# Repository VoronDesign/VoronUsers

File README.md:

# VoronUsers user mod repository

Welcome to VoronUsers. This is a place to share your mods for the VoronDesign 3D printers and find useful mods and resources from other Voron community members.

Check the [`printer_mods`](./printer_mods) folder for mods that apply to the current generation of printers. 

All mods that apply to older (=legacy) printers can be found in the [`legacy printers`](./legacy_printers) folder.

Mods where the authors have abandoned development can be found in the [`orphaned mods`](./orphaned_mods/) folder. If you want to start maintaining one of them, feel free to reach out via a [GitHub issue](https://github.com/VoronDesign/VoronUsers/issues/new/choose).

Looking to submit a mod? Check the [mod submission rules](https://github.com/VoronDesign/VoronUsers/wiki/Mod-Submission-Rules) and instructions on [how to submit to VoronUsers](https://github.com/VoronDesign/VoronUsers/wiki/How-to-Submit-to-VoronUsers)

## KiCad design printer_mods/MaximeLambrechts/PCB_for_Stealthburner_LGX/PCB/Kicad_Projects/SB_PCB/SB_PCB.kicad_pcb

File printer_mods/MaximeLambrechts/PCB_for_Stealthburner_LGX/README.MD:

# PCB for Voron Stealthburner & Bondtech LGX

This mod is a custom 2-piece PCB design, as well as a few printed parts, to make the Bondtech LGX fully compatible with the Voron Stealthburner.

This mod is based on two existing mods, all credits go to them for the initial design :

* LGX Stealthburner Mount Remix by Symataris on Thingiverse ([link here](https://www.thingiverse.com/thing:5242645))
* Stealthburner toolhead PCB by Hartk1213 ([link here](https://github.com/hartk1213/MISC/tree/main/PCBs/Stealthburner_Toolhead_PCB))

I really like the 2-piece PCB design by Hartk, with which you just plug the stealthburner in the main board via a connector, without having to deal with cables from the fans and LEDs.

Instead of trying to source different parts from different mods and make them all compatible with each other, I decided to create this mod and design 2 new PCB's (one for the stealthburner, one on the LGX), as well as the printed parts required to have a fully completed Stealthburner + LGX, as cleanly assembled as possible.

[1. Bill of Materials (BOM)](#1-bill-of-materials)

[2. Ordering PCBs](#2-ordering-pcbs)

[3. Printed parts](#3-printed-parts)

[4. Assembly Instructions](#4-assembly-instructions)

[5. Feedback](#5-feedback)

# 1. Bill of Materials (BOM)

Note: This BOM complements the original Stealthburner BOM. Only the extra compoments are included here. Items that are required for the original build are not included here. Refer to the stealthburner manual for a complete list of required components.

PCBs

* 1x Stealthburner side PCB (SB_PCB)
* 1x LGX side PCB (LGX_PCB)

Hardware

* 3x M3x6 Button head hex socket screws
* 1x 10mm standoff (female-female)
* 5x Heat set inserts (or 4 if using 2-hole cable chain)
* 1x M3x6 Socket head Cap Screws
* 2x M3x18 Socket head Cap Screws
* 2x M3x20 Socket head Cap Screws
* 2x M3x25 Socket head Cap Screws
* 2x M3x30 Socket head Cap Screws
* 2x M3x8 Flat head Screws (can be slightly longer, not critical)

Connectors & Electronics

* 1x Pin header, 6 pos, 2.54mm (Molex 22-28-4063)
* 1x Pin Socket, 6 pos, right angle through hole (Samtec SSW-106-02-G-S-RA)
* 1x Molex 43045-1600 (Board 16-pin receptacle)
* 1x Molex 43025-1600 (16-pin connector)
* 16x Molex 43030-0007 (contacts for wires)
* 2x Molex 43650-0200 (Hotend & Thermistor receptacles)
* 2x Molex 43645-0200 (Hotend & Thermistor connectors)
* 1x BAT85 diode (optional, if using probe only)
* 3x JST-PH 3-pin male & female
* 1x JST-PH 4-pin male & female

(Note: JST-PH connectors can be bought in assortment boxes on Amazon for example. I recommend this, as you would have multiple sizes in male/female in sufficient quantity for this and future projects, or should you need to recrimp a new cable for example)

Other

* 1x Small PTFE tube (2mm ID x 4mm OD) (length varies depending on your hotend. See assembly instructions).
* Small zipties

# 2. Ordering PCBs

Two Gerber zip files are provided for ordering the PCB's (**LGX_PCB_Gerber.zip** and **SB_PCB_Gerber.zip**).

I recommend JLCPCB or PCBWay for ordering the PCBs. I've personally ordered from JLCPCB and the boards were very cheap and worked perfectly.

An example order configuration for JLCPCB can be found [here](Pictures/PCB%20Order/JLCPCB.jpg).

An example order configuration for PCBWay can be found [here](Pictures/PCB%20Order/PCBWay.jpg).

Pay attention to the important settings (marked with an exclamation point) when ordering the PCB's!

The LGX PCB should be a **4-layer board of 1.6mm thickness**. (on JLCPCB only, you have to specify which layer is which, see picture)

The SB PCB should be a **2-layer board of 1.6mm thickness**.

Other parameters are personal preference, like the color of the board, or if you want lead-free HASL for example.

# 3. Printed parts

The following parts need to be (re)printed :

* **Stealthburner_Body.stl** (There are small differences to the original file. Some small cutouts for a better PCB fit and the PCB mounting
points have been modified.)
* **LGX_Mount.stl**
* **LGX_Rear_PCB_Support.stl**
* **Cover.stl**
* **Cable_Chain_Anchor_xHoles..stl** (Chose either the 2 or 3-hole version depending on your cable chain)

# 4. Assembly Instructions

Note: These instructions are a complement to the original Stealthburner assembly manual. Keep a copy of the original manual open in parallel 
to these instructions, as I will often refer to it.

## Preparing the PCBs

* Solder the components on the LGX pcb as shown on the picture. Make sure the 6-pin socket lays nice and flat on the PCB and is soldered straight. This is important for correct connection with the stealthburner later on.

* If you're not using an inductive probe (for example Klicky or KlickyNG mod with microswitch), replace the BAT85 diode by a small piece
of wire to short the pads. A leg from a donor component (LED or resistor for example) works well here.

* Install a 10mm standoff using an M3x6 button head screw.
Make sure the screw head **does not stick out more than 2mm from the PCB**.
Make sure **no solder points stick out more than 2mm**. (to avoid touching and potentially shorting on the LGX extruder motor later on)

* Solder a 6-pin header to the SB PCB. The pins should face up.

## Stealthburner

* Follow the original manual instructions to install the LED's and fans into the stealthburner body. Leave the cables hanging for now.

* Install the PCB into the SB body and fasten with 2 M3x6 button head screws.
**Warning**: Do not overtighten as these screw into plastic.

* Make sure the screws do not stick out of the SB body, or there would be a clearance issue with the LGX. (That's the reason why button head screws are used here instead of socket head)

* Solder all the wires onto the PCB as shown on the picture below. Note: The red (positive) wire of both fans can be soldered to either 24V or 5V 
depending on the voltage of your fans.

## Printhead

* Follow the stealthburner manual to assemble the printhead. You can print either the CW1 or CW2 version of the printed parts.

* Install the PTFE tube into the hotend. The length of the tube will vary depending on your hotend. The tube should stick out **25mm** from the top of the printed part.

## LGX

* Install 2 heat set inserts into the LGX Mount as shown. 
Install 2 (or 3) heat set inserts into the cable chain anchor as shown.

* dissasemble the front part of your LGX extruder.

* On the backside, remove the 2 left screws.

* Slide the LGX_Mount onto the LGX extruder and fasten with 2 M3x20 on the bottom and two M3x27 (original screws from LGX) on the front.

* Slide the PCB into the LGX_Mount printed parts grooves until it is fully seated into place.

* Install the PCB rear support printed part. It should slide onto the PCB and insert into the holes of the extruder motor.

* Install the cable chain anchor and fasten everything together with 2 M3x25 screws.

* Now is a good time to make sure no solder points touch the LGX extruder motor.

## Final Assembly

* Follow the stealthburner manual to install the carriage and probe (or klicky).

* Fasten the LGX assembly onto the carriage with 2 M3x30 screws.
Make sure the probe wires are routed correctly and are not pinched between the carriage and LGX.

* Slide the printhead from the bottom into the LGX assembly. Make sure it is fully inserted, flush with the LGX mount, and flush on the X-carriage.

* Slide the Stealthburner in place. Make sure the pins align correctly with the socket. It is recommended to first align and insert the pins, then slide the SB fully in place.

* Fasten the Stealthburner with 2 **M3x18** screws on top, and 2 **M3x50** screws on the bottom.

* Prepare a small cable for the extruder motor with JST-PH connectors as shown. Its length should be about **90mm**.

* Install the extruder motor cable.

* Wire up the rest of the components, including the hotend, thermistor, probe or switch, etc

* Fasten the cable chain with 2 M3x8 flat head screws.
Install a ziptie into the ziptie slot.

* Wire up and install the 16-pin connector. The wiring schematic is the same as the original Hartk PCB. The only difference is that the 14 and 2-pin connectors have been joined into a single 16-pin connector. The individual wires position is identical. See the wiring instructions [here](https://github.com/hartk1213/MISC/tree/main/PCBs/Stealthburner_Toolhead_PCB/Images/Wiring).

* Optionally, install a chamber thermistor. I've attached mine at the backside on the cable chain and routed the wires to the AUX connector on the PCB.

* Install the cover by sliding the backside over the M3 screws sticking out of the LGX, and then fasten on the side with 1 **M3x6** Socket head Screw.

## Done ! Happy printing!

# 5. Feedback

While I've manage to assemble everything on my printer, there may be issues I haven't thought of, mistakes on this page, or issues that will only arise after many hours of printing.

**USE THIS MOD AT YOUR OWN RISK!**

I'd appreciate any kind of feedback, good or bad.

If you encounter issues, please open an issue on this github page.

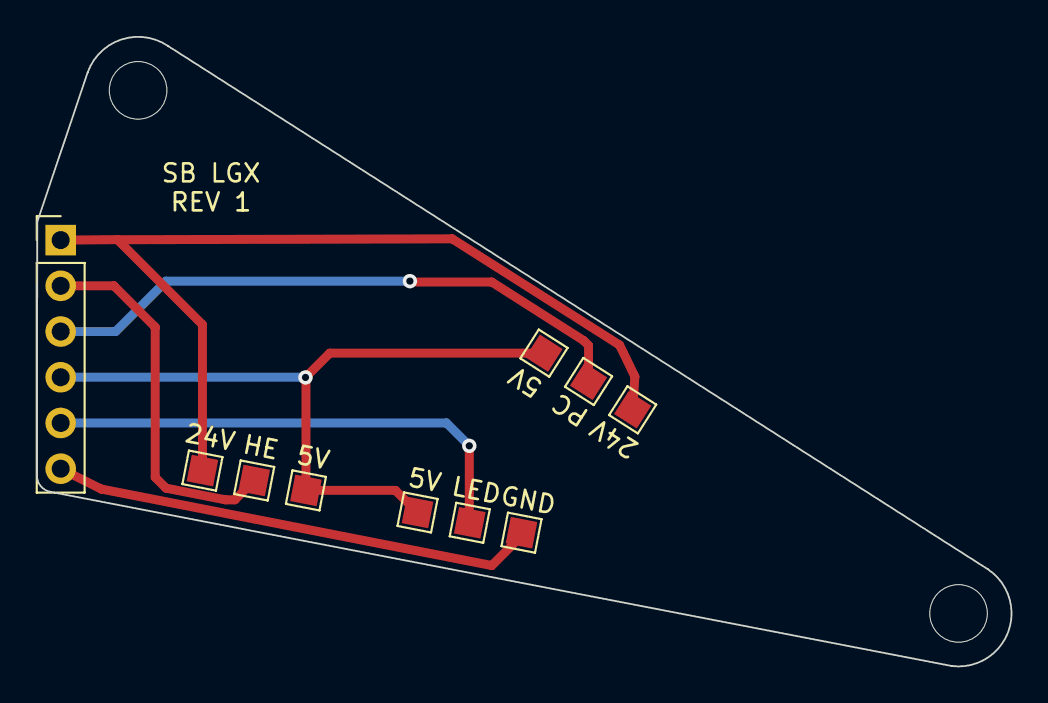
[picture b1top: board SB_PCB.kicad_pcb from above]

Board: 2 copper layers, 54.1 x 35.0 mm, 12 parts (0 on the bottom side), 6 nets.

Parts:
5V: 5V PC Fan; TestPoint_Pad_1.5x1.5mm
5V#2: 5V HE Fan; TestPoint_Pad_1.5x1.5mm
5V#3: Solder Pad 5V; TestPoint_Pad_1.5x1.5mm
24V: 24V HE Fan; TestPoint_Pad_1.5x1.5mm
24V#2: 24V PC Fan; TestPoint_Pad_1.5x1.5mm
GND: Solder Pad GND; TestPoint_Pad_1.5x1.5mm
H1, H2: MountingHole; MountingHole_3.2mm_M3
HE: GND HE Fan; TestPoint_Pad_1.5x1.5mm
J1: Pin Header; PinHeader_1x06_P2.54mm_Vertical
LED: Solder Pad LED; TestPoint_Pad_1.5x1.5mm
PC: GND PC Fan; TestPoint_Pad_1.5x1.5mm

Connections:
5V: 5V.1, 5V#2.1, 5V#3.1, J1.4
24V: 24V.1, 24V#2.1, J1.1
GND: GND.1, J1.6
HE FAN: HE.1, J1.2
LED: J1.5, LED.1
PC FAN: J1.3, PC.1

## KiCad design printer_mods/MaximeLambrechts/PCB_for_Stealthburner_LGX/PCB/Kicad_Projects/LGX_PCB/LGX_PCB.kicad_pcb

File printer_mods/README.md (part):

# Mods

Printer mods for Voron 3D printers
---

| Creator | Mod title | Description | Printer compatibility | Last Changed |
| --- | --- | --- | --- | --- |
| 1-0-R | [V2.4 handle](1-0-R/handle) | Handle for Voron 2.4 | V2.4 | 2024-01-08T16:38:25+00:00 |
| 120decibell | [Side entry exhaust housing](120decibell/exhaust_housing_side_entry) | Exhaust housing with dual cover screws and single or dual side... | V1.8, V2.4, VT | 2024-01-08T16:38:25+00:00 |
|  | [Huvud Chain Mount](120decibell/huvud_chain_mount) | Huvud rear mount for Clockwork or LGX that supports a cable chain. | V1.8, VT | 2024-01-08T16:38:25+00:00 |
| 3dpandme | [FANnypack zero](3dpandme/Fannypack_zero) | Electronics cooling solution for Voron Zero | V0.2, VSW, VT | 2024-01-08T16:38:25+00:00 |
|  | [Thermistor holder zero](3dpandme/Thermistor_holder_zero) | Extended thermistor holder for Voron Zero | V0.2, VSW, VT | 2024-01-08T16:38:25+00:00 |
| 3vilson | [V0.1_Skirt_Holes](3vilson/V0.1_Skirt_Holes) | Skirt with Access Holes from the bottom | V0.2 | 2024-01-08T16:38:25+00:00 |
|  | [V0.1_Skirt_Inlet](3vilson/V0.1_Skirt_Inlet) | Skirt with C14 inlet + New feet to screw into | V0.2 | 2024-01-08T16:38:25+00:00 |
| 42bios | [Corner panel clip w. cable](42bios/corner_panel_clip_cable) | Corner panel clip with an internal cable path. | V2.4 | 2024-01-08T16:38:25+00:00 |
|  | [Exhaust filter housing - side...](42bios/exhaust_filter_housing_side) | Exhaust filter housing with the G1-8 "thread on the side. | V2.4 | 2024-01-08T16:38:25+00:00 |
|  | [relay mount](42bios/relay_mount) | relay-mount for 2x 2 channel relay modules. | V2.4 | 2024-01-08T16:38:25+00:00 |
| ademuri | [Lights, Camera, Voron](ademuri/Lights_Camera_Voron) | A mount for LED strips and Picam for the V0.1 | V0.2 | 2024-01-08T16:38:25+00:00 |
| aeresov | [Ballpoint pen spring DIN clips](aeresov/ballpoint-pen-spring-DIN-clips) | Assortment of mechanical DIN clips using common ballpoint pen springs. | V2.4r2, VT | 2024-06-19T10:47:27+00:00 |
|  | [cable tie DIN mount](aeresov/cable_tie_DIN_mount) | A bracket for cable ties to route cables across DIN rails. | V2.4 | 2024-01-08T16:38:25+00:00 |
|  | [MeanWell UHP-xxx DIN mount](aeresov/MeanWell_UHP_DIN_mount) | A bracket for MeanWell UHP series PSU (200, 350 and 500) to mount... | V2.4 | 2024-01-08T16:38:25+00:00 |
|  | [Raspberry Pi DIN mount](aeresov/Raspberry_Pi_DIN_mount) | A bracket for Raspberry Pi 3/4 to mount it onto DIN rail, along or... | V2.4 | 2024-01-08T16:38:25+00:00 |
|  | [SKR 1.3/1.4 DIN mount](aeresov/SKR_DIN_mount) | A bracket for SKR 1.3/1.4 board to mount it onto DIN rail, along or... | V2.4 | 2024-01-08T16:38:25+00:00 |
|  | [TL filament sensor bracket](aeresov/TL_filament_sensor_bracket) | A bracket for TL filament sensor to mount near stock spool holder. | V2.4 | 2024-01-08T16:38:25+00:00 |
| Akio | [Hidden cable routing z belt cover](Akio/cable_routing_z_belt_cover) | Z belt covers that allow hidden cable routing. | V2.4 | 2024-01-08T16:38:25+00:00 |
| al3ph | [Analog Timer Mount](al3ph/analog_timer_mount) | A skirt mount for analog timer | V0.2 | 2024-01-08T16:38:25+00:00 |
|  | [Filament Runout Sensor](al3ph/filament_runout) | A simple filament runout sensor | V0.2, V1.8, V2.4, VSW | 2024-01-08T16:38:25+00:00 |
|  | [LED Mount](al3ph/led_mount) | A mount for 10mm LED WS2812 strips | V0.2 | 2024-01-08T16:38:25+00:00 |
|  | [PL05 Sensor Mount](al3ph/pl05_mount) | A mount PL05 inductive sensor | V0.2 | 2024-01-08T16:38:25+00:00 |
| alanho | [BTT PITFT50 v2 Mount](alanho/BTT_PITFT50_v2_Mount) | A mount for the BTT PITFT50 v2 Touch Display | V2.4 | 2024-01-08T16:38:25+00:00 |
| albert | [IKEA Dioder Led Mount](albert/IKEA_Dioder_Led_Mount) | A mount for the IKEA Dioder LED strip | V2.4 | 2024-01-08T16:38:25+00:00 |
| AlexanderT-Moss | [270 Clamping Hinges](AlexanderT-Moss/270-Clamping-Hinges) | Simple 270 degree hinges that clamp to the front panels instead of... | V2.4 | 2024-01-08T16:38:25+00:00 |
| Andre | [Mini Afterburner ADXL345 Mount](Andre/Mini_Afterburner_ADXL345_Mount) | Mount for an AXDL345 on the Mini Afterburner | V0.2 | 2024-01-08T16:38:25+00:00 |
|  | [Mini Afterburner Strain Relief](Andre/Mini_Afterburner_Strain_Relief) | A replacement strain relief for the Mini Afterburner toolhead | V0.2 | 2024-01-08T16:38:25+00:00 |
|  | [Revo Nozzle Skirt](Andre/Revo_Nozzle_Skirt_Trident) | A Revo nozzle box hidden in a Trident skirt. | VT | 2024-01-08T16:38:25+00:00 |
|  | [V0 Neopixel Front Bed Mount](Andre/V0_Neopixel_Front_Bed_Mount) | A replacement Front Bed Mount with room for a neopixel or dotstar... | V0.2 | 2024-01-08T16:38:25+00:00 |
| antoinecellerier | [DS18B20 Sensor Mount](antoinecellerier/ds18b20-sensor-mount) | DS18B20 temperature sensor mount | V0.2 | 2024-01-08T16:38:25+00:00 |
| ardichoke | [V0 Long Thumb Nut](ardichoke/v0-long-thumb-nut) | Taller thumb nuts for V0 bed | V0.2 | 2024-01-08T16:38:25+00:00 |
| arkeet | [Dial test indicator mount](arkeet/dti-mount) | A toolhead mount for a dial test indicator, where the tip is... | V1.8, V2.4 | 2024-01-08T16:38:25+00:00 |
|  | [Magnetic hotend fan cover](arkeet/magnet-fan-cover) | A replacement hotend fan cover, held with magnets instead of screws. | V1.8, V2.4, VSW | 2024-01-08T16:38:25+00:00 |
|  | [MGN12 X-axis](arkeet/mgn12) | Replaces the dual MGN9H rails with a single MGN12H. | V2.4 | 2024-01-08T16:38:25+00:00 |
|  | [V0 DC inlet](arkeet/v0-dc-inlet) | Skirt inlet for external 24V DC power supply. | V0.2 | 2024-01-08T16:38:25+00:00 |
| aTinyShellScript | [RS PSU DIN Bracket](aTinyShellScript/RS_PSU_DIN_Brackets) | DIN brackets for MeanWell RS PSUs with 80mm spacing. | V2.4 | 2024-01-08T16:38:25+00:00 |
| AVieira | [Universal_Phone_Mount](AVieira/Universal_Phone_Mount) | This mod allows the use of different smartphones or possibly... | V2.4r2 | 2024-01-08T16:38:25+00:00 |
| baccula | [Revo Nozzle Holder for v2.4 350](baccula/revo_skirt_nozzle_holder) | A remix of Andre's design allowing for skirt storage of 4 E3D Revo... | V2.4 | 2024-01-08T16:38:25+00:00 |
| Backenfutter | [Mount for Electreeks Camera](Backenfutter/Mount_for_Electreeks_Camera) | This Mod is a simple "One Piece" mount for the popular Electreeks... | V2.4 | 2024-01-08T16:38:25+00:00 |
| Badnoob | [AB-BN Afterburner mod (5015)](Badnoob/AB-BN) | Improved Afterburner with 5015 fan | V1.8, V2.4, VSW, VT | 2024-01-08T16:38:25+00:00 |
|  | [AB-BN for Stock Afterburner (4020)](Badnoob/ABBN_for_Stock) | Improved Dragon and Rapido toolhead for stock Afterburner with 4020... | V1.8, V2.4, VSW, VT | 2024-01-08T16:38:25+00:00 |
|  | [Precision AB Drive](Badnoob/Precision_AB_Drive) | Changes the gearing for the AB drives to improve both resolution... | V2.4 | 2024-01-08T16:38:25+00:00 |
| Baltojikale | [LoudOwl aka Stabby](Baltojikale/LoudOwl_aka_Stabby) | Alternative dual 5015 part cooling fan toolhead for Afterburner | V1.8, V2.4, VSW | 2024-01-08T16:38:25+00:00 |
| beaugalbraith | [Nova Printhead](beaugalbraith/Nova_Printhead) | Use Nova Hotend with Afterburner | V2.4 | 2024-01-08T16:38:25+00:00 |
| BladeScraper-Designs | [CornerPanel_SpoolHolder](BladeScraper-Designs/CornerPanel_SpoolHolder) | A better supported Spool Holder that mounts to a modified corner... | V0.2 | 2024-01-08T16:38:25+00:00 |
|  | [Horizontal Spool Holder](BladeScraper-Designs/Horizontal-Spool-Holder) | Based on the stock holder but mounts to the horizontal extrusions. | V2.4 | 2024-01-08T16:38:25+00:00 |
|  | [Microswitch Pod With Connector](BladeScraper-Designs/Microswitch_Pod_With_Conector) | Microswitch pod with JST-XH 4-pin connector | V2.4 | 2024-01-08T16:38:25+00:00 |
| Blamm | [LRS-100 DIN mount](Blamm/lrs-100) | DIN rail mount for an extra LRS-100 Power Supply | V1.8, V2.4, VT | 2024-01-08T16:38:25+00:00 |
| BlueBear | [Bowden Fence](BlueBear/Bowden_Fence) | A little "fence" to hold the tubes away from the belts. | V0.2 | 2024-01-08T16:38:25+00:00 |
|  | [Deck Panel Backpack](BlueBear/Deck_Panel_Backpack) | A mounting alternative if you don't want to drill your deck panel | V0.2 | 2024-01-08T16:38:25+00:00 |
|  | [Clippable Wago 221 Mounts](BlueBear/Wago_221_mount) | Mounts for Wago 221 to screw or clip-in on 1515 extrusions | V0.2 | 2024-01-08T16:38:25+00:00 |
|  | [Ziptie Mount](BlueBear/Ziptie_Mount) | Clippable Ziptie hooks for 1515 extrusions | V0.2 | 2024-01-08T16:38:25+00:00 |
| bobbleheed | [Filament Runout Sensor](bobbleheed/Filament_Runout) | Filament runout sensor that replaces the stock bowden retainer | V1.8, V2.4, VT | 2024-01-08T16:38:25+00:00 |
|  | [Magnetic Panels](bobbleheed/Magnetic_Panels) | Magnetic clips to allow for easy removal and installation of panels | V2.4 | 2024-01-08T16:38:25+00:00 |
| Boingomw | [Wago mount](Boingomw/Wago_mount) | Smaller 5 port Wago mount that fits parallel to the support rails | V2.4 | 2024-01-08T16:38:25+00:00 |
| Bondtech | [Mini-After-LGX-Lite](Bondtech/Mini-After-LGX-Lite) | LGX Lite Toolhead Setup For Voron V0.1. | V0.2 | 2024-01-08T16:38:25+00:00 |
| btp | [Galileo chain mount (befenybay)](btp/Galileo_Switchwire_Chain_Mount) | Modified chain mount position to cater for difference with Galileo... | VSW | 2024-01-08T16:38:25+00:00 |
| buzzdalf | [v1.8/2.4 Afterburner connector...](buzzdalf/connector_cover) | v1.8/2.4 Connector cover for 42STH20-1004AS | V1.8, V2.4 | 2024-01-08T16:38:25+00:00 |
|  | [Ender 3 Switchwire Taller Z Mod](buzzdalf/ender_switchwire_taller_z) | Taller Z Mod | VSW | 2024-01-08T16:38:25+00:00 |
|  | [Ender 3 Switchwire Y Tensioner Mod](buzzdalf/ytension) | Y Tension Mod | VSW | 2024-01-08T16:38:25+00:00 |
| ByteChild | [2-Channel Relay DIN Rail Bracket](ByteChild/2_Channel_Relay_DIN_Rail_Bracket) | DIN Rail mounting bracket for an 2-Channel-Relay | V2.4 | 2024-01-08T16:38:25+00:00 |
|  | [ESP32 DIN Rail Bracket](ByteChild/ESP32_DIN_Rail_Bracket) | DIN rail mounting bracket for an ESP32 | V2.4 | 2024-01-08T16:38:25+00:00 |
| bythorsthunder | [MGN9 Backers Idlers](bythorsthunder/MGN9_Backers) | New idler uppers for MGN9 Extrusion backers | V2.4 | 2024-01-08T16:38:25+00:00 |
|  | [Stealthburner Rapido UHF](bythorsthunder/Stealthburner_Rapido_Uhf) | Stealthburner mod for Rapido UHF | V2.4, VSW, VT | 2024-01-08T16:38:25+00:00 |
| CannedBass | [PITFT50 45-degree mount](CannedBass/PITFT50_45_degree_mount) | Mount that puts the screen at a 45-degree angle for more vertical... | V2.4, VT | 2024-01-08T16:38:25+00:00 |
|  | [Trident Bed Fans](CannedBass/Trident_Bed_Fans) | Bed fans for Trident | VT | 2024-01-08T16:38:25+00:00 |
| Ch4rlesB | [V0 Handles Slim](Ch4rlesB/V0_Handles_Slim) | Simple and slim handles for the V0 | V0.2 | 2024-01-08T16:38:25+00:00 |
| ChenTheDesignMaker | [Z Belt Clip](ChenTheDesignMaker/Z_Belt_Clip) | Simple clip to keep extra Z belts clean and away from panels | V2.4 | 2024-01-08T16:38:25+00:00 |
| chirpy | [V0.1 Nozzle Wiper](chirpy/NozzleWiper) | Servo powered nozzle wiper and purge bucket | V0.2 | 2024-01-08T16:38:25+00:00 |
|  | [Runout UnKlicky Sensor](chirpy/RunoutUnklicky) | Runout UnKlicky Sensor is a filament runout sensor with mounts for... | V0.2, V1.8, V2.4, VSW, VT | 2024-01-08T16:38:25+00:00 |
|  | [V0.1 Raised Tophat](chirpy/TipTophat) | Alternative Tophat design that uses stock panels and raises height... | V0.2 | 2024-01-08T16:38:25+00:00 |
| chri.kai.in | [20x20mm Profile Covers](chri.kai.in/20x20mm_Profile_Covers) | Provide overlapping and flush slot covers for 20x20mm slot6... | V1.8, V2.4, VSW, VT | 2024-01-08T16:38:25+00:00 |
|  | [Angry CAM USB](chri.kai.in/Angry_CAM_USB) | Housing for small USB camera module, allowing mounting to gantry or... | V2.4 | 2024-01-08T16:38:25+00:00 |
|  | [Exhaust Adapter 100mm](chri.kai.in/Exhaust_Adapter_100mm) | Replace 60mm exhaust fan with 100mm ventilation system adapter | V1.8, V2.4, VT | 2024-01-08T16:38:25+00:00 |
| chrisrgonzales | [270° Front Panel Hinge](chrisrgonzales/270_degree_hinge) | Hinges that have 270° of swivel, parametric CAD included | V2.4 | 2024-01-08T16:38:25+00:00 |
| christophmueller | [Phaetus and Zodiac Dragonfly BMO...](christophmueller/Phaetus_Dragonfly_BMO_Afterburner) | Covers both the original Phaetus variant as well as the Zodiac one. | V1.8, V2.4, VSW | 2024-01-08T16:38:25+00:00 |
| claytono | [Voron 2.4 Extrusion Jig](claytono/2.4-extrusion-jig) | A jig help align extrusions to get a properly square frame | V2.4 | 2024-01-08T16:38:25+00:00 |
|  | [Fysetc S6 V2 Mount](claytono/fysetc-s6-v2-mount) | DIN Mount for the Fysetc S6 V2 controller | V1.8, V2.4 | 2024-01-08T16:38:25+00:00 |
|  | [V0 Zip Tie Skirts](claytono/v0-zip-tie-skirts) | V0 skirts with small loops added along the top to allow zip tyiing... | V0.2 | 2024-01-08T16:38:25+00:00 |
| clee | [Monster8 DIN Rail Mounts](clee/Monster8_heatsert_mount) | DIN mount for Makerbase Monster8 V1/V2 controller | V2.4, VT | 2024-01-08T16:38:25+00:00 |
| cmrny | [V0.1 Motor Panel Modification](cmrny/v01_motor_panel_no_rub) | V0.1 Motor panel modification to keep umbilical and bowden tube... | V0.2 | 2024-01-08T16:38:25+00:00 |
| conqueror433 | [Voron Parts Logo](conqueror433/Voron_Parts_Logo) | Voron Parts Logo for your back panels, 3D Print or Laser Cut | V2.4 | 2024-01-08T16:38:25+00:00 |
|  | [Voron V0.1 Parts Logo](conqueror433/Voron_V0.1_Parts_Logo) | Voron Parts Logo for your V0 deck panel | V0.2 | 2024-01-08T16:38:25+00:00 |
| consibonsi | [Y-Mod SW 9mm](consibonsi/Y-Mod_SW_9mm) | 9mm Y belt mod for SW | VSW | 2024-01-08T16:38:25+00:00 |
| crackzero_akl | [RapidoTZ Hotend Stealthburner](crackzero_akl/RapidoTZ_Hotend) | Construction Guide to transform Bambu Lab TZ 2.0 hotend to Rapido V2.0-like hotend | V0.2, V1.8, V2.4, VT, VSW | 2024-01-08T16:38:25+00:00 |
| csch0 | [SW Fan Mount No Tape](csch0/SW_FanMount_No_Tape) | 60x20 Fan Mount for SW without tape | VSW | 2024-01-08T16:38:25+00:00 |
| d3nny | [Filtered Power Plug with...](d3nny/mains_plug_panel_for_RND_165-00057) | Filtered Power Plug for RND 165-00057 and CAT6-Plug | V2.4 | 2024-01-08T16:38:25+00:00 |
| D4rkCelerity | [Raspberry Pi Zero Bracket](D4rkCelerity/Raspberry_Pi_Zero_Bracket) | Modified version of Trident RPi bracket to fit the smaller RPi Zero | V0.2, V1.8, V2.4, VT | 2024-01-08T16:38:25+00:00 |
| DaGlo | [V0.1 Duet 2 Wifi mounting brackets](DaGlo/Voron_V0_Duet_2_WiFi_Mounting_Brackets) | Voron 0.1 Mounting brackets with/without RPi 4 | V0.2 | 2024-01-08T16:38:25+00:00 |
|  | [Voron V0 Mean Well power supply...](DaGlo/Voron_V0_MW_PS_Bracket) | Voron V0 Mean Well power supply bracket (Funssor Kit) | V0.2 | 2024-01-08T16:38:25+00:00 |
|  | [Voron V0 SSR Mount](DaGlo/Voron_V0_SSR_Mount) | Voron V0 SSR Mount for the bottom | V0.2 | 2024-01-08T16:38:25+00:00 |
| DaGrooch13 | [Tophat Exhaust Filter V0](DaGrooch13/Tophat_Exhaust_Filter) | Activated charcoal exhaust filter with HEPA that replaces the rear... | V0.2 | 2024-01-08T16:38:25+00:00 |
| Dan88 | [V0 one-part Skirts](Dan88/V0skirt) | One part Skirts for the V0 | V0.2 | 2024-01-08T16:38:25+00:00 |
| dankeeling | [Creative Live! Camera Mount](dankeeling/CreativeLiveCameraMount) | A mod to provide a mount for the Creative Live! Camera that mounts... | V2.4r2, VT | 2024-01-08T16:38:25+00:00 |
| DaStivi | [The Cephalopod limb (BTT Octopus...](DaStivi/the_Cephalopods_limb) | An alternative Din rail mount for BTT Octopus (PRO) boards | V1.8, V2.4, VSW, VT | 2024-01-08T16:38:25+00:00 |
| Daten | [Revo hotend skirt case](Daten/Voron_2.4_Revo_Nozzle_Holder) | A skirt case for the Revo hotends to reside R1 and R2 | V2.4 | 2024-01-08T16:38:25+00:00 |
| davidauvergne | [Center_cable_management_duct](davidauvergne/Center_cable_management_duct) | Mod for a centered cable management | V2.4 | 2024-01-08T16:38:25+00:00 |
| DC67 | [Plug Panel Mod for Schaffner...](DC67/plug_panel_schaffner) | A modified plug panel for the Power Entry Connector Schaffner... | V2.4 | 2024-01-08T16:38:25+00:00 |
| deepfriedheroin | [v0 Wago Bed Mounts](deepfriedheroin/v0_bed_wagos) | Easy to install Wago mounts for the v0 | V0.2 | 2024-01-08T16:38:25+00:00 |
|  | [v0 Power Wagos](deepfriedheroin/v0_power_wagos) | Easy to install Wago mounts for v0 mains | V0.2 | 2024-01-08T16:38:25+00:00 |
|  | [V2 Bed Wagos](deepfriedheroin/v2_bed_wagos) | Wire management for the v2 bed | V2.4 | 2024-01-08T16:38:25+00:00 |
| dePrintinator | [HEPA Exhaust](dePrintinator/HEPA_Filter_Exhaust) | HEPA filter chamber exhaust replacement. | V1.8, V2.4, VT | 2024-01-08T16:38:25+00:00 |
| DerekBackus | [LED Strip Holder](DerekBackus/LED_Holder) | Simple bracket to mount an LED strip | V2.4, VT | 2024-01-21T20:17:15+00:00 |
|  | [Trident Right Skirt Switch](DerekBackus/Right_Skirt_Switch) | Moves power switch to right front skirt on the Trident | VT | 2024-01-21T20:17:15+00:00 |
| Derpimus | [V0.1 Block Handle](Derpimus/Block_handle_v0.1) | V0.1 Block Style Handle | V0.2 | 2024-01-08T16:38:25+00:00 |
| DorjeDorf | [Duet 3 3HC Din Bracket](DorjeDorf/Duet_3_3HC_Din_Bracket) | V2.4 Duet 3 3HC Din Bracket | V2.4 | 2024-01-08T16:38:25+00:00 |
|  | [Duet 3 6HC Din Bracket](DorjeDorf/Duet_3_6HC_Din_Bracket) | V2.4 Duet 3 6HC Din Bracket | V2.4 | 2024-01-08T16:38:25+00:00 |
| doubletrouble | [V0 Skirt Mod](doubletrouble/V0_Skirt_Mod) | V0 Skirt Mod | V0.2 | 2024-01-08T16:38:25+00:00 |
| Dr-Info | [BTT 5160T Plus Mounts](Dr-Info/BTT_5160T_Plus_Mounts) | Mounts for BTT 5160T Plus to DIN, 2020 and 1515 | V2.4, VT | 2024-02-01T10:07:10+00:00 |
|  | [Corner Cable Cover with Drop Holes](Dr-Info/corner_cable_cover_with_drop_down_holes) | Corner cable cover around Z-idler with drop holes near z frame and... | V2.4, VT | 2024-02-01T10:07:10+00:00 |
|  | [Lever Connector Mount Side Fan...](Dr-Info/Lever_Connector_Mount_Side_Fan_Support) | Mount Universal Lever Connectors or WAGO 221 using the side fan... | V2.4, VT | 2024-02-01T10:07:10+00:00 |
|  | [LRS DIN Mount Offset](Dr-Info/LRS_DIN_Mount_Offset) | Offset mount for LRS PSU on DIN rail with stabilizer | V2.4, VT | 2024-02-01T10:07:10+00:00 |
|  | [V2.4 Z Drive Motor Tensioner Mod](Dr-Info/V2.4_z_drive_motor_tensioner_mod) | Braced motor tensioner for z drive | V2.4r2 | 2024-02-23T17:05:57+00:00 |
|  | [V2.4 Rear Skirt Mod for Z-Drive...](Dr-Info/V2.4r2_Z-Drive_Motor_Tensioner_Mod_Rear_Skirts) | This mod enables the you to utilize the rear skirts, power and... | V2.4 | 2024-01-08T16:38:25+00:00 |
| DrGhetto | [Ghetto Panels](DrGhetto/GhettoPanels) | Printed panels for the Voron Zero | V0.2 | 2024-01-08T16:38:25+00:00 |
| eamars | [Stealthburner (RC1) Dragon...](eamars/stealthburner_crazy_dragon_toolhead) | The Stealthburner toolhead mount for Mellow Crazy, TriangleLab... | V1.8, V2.4, VSW, VT | 2024-01-08T16:38:25+00:00 |
| eddie | [LED Bar Clip](eddie/LED_Bar_Clip) | Modular LED Clip for mounting LED Strip to 2020 Extrusions | V1.8, V2.4, VT | 2024-01-08T16:38:25+00:00 |
|  | [V1.8 12mm Z Mod](eddie/V1.8_12mm_Z_Mod) | Add V1.8 option for 12mm Z rods | V1.8 | 2024-01-08T16:38:25+00:00 |
| edwardyeeks | [Tridentified V2.4 Power Inlet](edwardyeeks/Tridentified_V2.4_Power_Inlet) | Trident style side power inlet for V2.4 using Z Drive Motor... | V2.4 | 2024-01-08T16:38:25+00:00 |
| elcrni | [Trident Internal Spool Holder](elcrni/Trident_Internal_Spool_Holder) | Internal spool holder for 300 and 350 Tridents. Supports full size... | VT | 2024-01-08T16:38:25+00:00 |
|  | [V.24/Trident Spool Holder](elcrni/V2.4-Trident-Spool-Holders) | Spool holder that mounts on top for "too close to the wall" printers | V1.8, V2.4, VT | 2024-01-08T16:38:25+00:00 |
| Electroleon | [U2C Mounting](Electroleon/U2C_Mounting) | Bigtreetech U2C CAN Interface mounting bracket | V0.2, V1.8, V2.4, VT | 2024-01-08T16:38:25+00:00 |
| Ellis | [15x15 Drag Chain End](Ellis/15x15_Drag_Chain_End) | 15x15 drag chain end piece | V2.4 | 2024-01-08T16:38:25+00:00 |
|  | [Badge Retractor Mount](Ellis/Badge_Retractor_Mount) | Extrusion mount for badge retractor to keep bowden tube out of the... | V2.4 | 2024-01-08T16:38:25+00:00 |
|  | [Bed Fans](Ellis/Bed_Fans) | Bed fan control macros and 5015 bed fan mounts | V2.4 | 2024-01-08T16:38:25+00:00 |
|  | [Short Z Joints](Ellis/Short_Z_Joints) | Shorter Z joints for the v2.4 | V2.4 | 2024-01-08T16:38:25+00:00 |
|  | [Single MGN9H Carriage](Ellis/Single_MGN9H_Carriage) | Single MGN9H toolhead carriage with toolhead x endstop support (for... | V1.8, V2.4 | 2024-01-08T16:38:25+00:00 |
| ElPoPo | [Removable Doors](ElPoPo/RemovableDoors) | New hinge to easily remove the door and have a wide opening V2.x | V2.4 | 2024-01-08T16:38:25+00:00 |
| EmJay276 | [Stealthburner Phaetus Dragon UHF...](EmJay276/stealthburner_dragon_UHF_toolhead) | This mod adds a tool cartridge for the Phaetus Dragon UHF and... | V2.4, VT | 2024-01-08T16:38:25+00:00 |
| Empusas | [Mounts for BTT Filament Motion...](Empusas/BTT_Filament_Motion_Sensor_Mount) | Mounts for Big Tree Tech Smart Filament Motion Sensor | V0.2, V1.8, V2.4, VSW | 2024-01-08T16:38:25+00:00 |
|  | [Power Skirt 2.x FN284-10-06](Empusas/PowerSkirt_FN284-10-06) | Power Skirt for Schaffner FN284-10-06 V2.x | V2.4 | 2024-01-08T16:38:25+00:00 |
|  | [Mounts for Terminal Blocks NC933...](Empusas/Terminal_Blocks_NC933_SPL-62) | Mounts for Terminal Blocks NC933 and SPL-62 from AliExpress | V2.4 | 2024-01-08T16:38:25+00:00 |
| evandepol | [Crydom GN Terminal Guard](evandepol/Crydom-GN-Guard) | A simple safety guard for the terminals on a Crydom GN SSR | V2.4 | 2024-01-08T16:38:25+00:00 |
|  | [Voron 2.4 cable clamps](evandepol/Voron2.4-Cable-clamps) | A set of 2020-mounted cable guards to organize and dress the wiring... | V2.4 | 2024-01-08T16:38:25+00:00 |
| falo | [LGX Lite CAN Side Mount](falo/lgx_lite_side_can) | A side mounting for a CAN board (Huvud/SHT42) to the LGX Lite | V1.8, V2.4, VSW, VT | 2024-01-08T16:38:25+00:00 |
|  | [Magnetic Exhaust Grill Cover](falo/magnetic_grill_cover) | A magnetic cover to seal the filtered exhaust | V2.4 | 2024-01-08T16:38:25+00:00 |
|  | [Toolhead PCB to CAN Mount Adaptor](falo/toolhead_pcb_to_can) | A mount to enable side mounting of a CAN board (Huvud/SHT42) in... | V1.8, V2.4, VSW, VT | 2024-01-08T16:38:25+00:00 |
| Ferdi360 | [2.4 Bedfan Backplates](Ferdi360/2.4_Bedfan_Backplates) | Backplates for your Voron 2.4 that block hot air out of your... | V2.4r2 | 2024-01-08T16:38:25+00:00 |
| Fiction | [C270 mount](Fiction/C270_mount) | Logitech C270 webcam front-centre mount | V2.4, VT | 2024-01-08T16:38:25+00:00 |
|  | [Crossrail](Fiction/Crossrail) | Across-the-rails LRS-200-24 or RSP-200-24 mount using DRP-03 brackets | V2.4, VT | 2024-01-08T16:38:25+00:00 |
|  | [Exhaust_cover](Fiction/Exhaust_cover) | Cover for exhaust cutout in back panel | V2.4, VT | 2024-01-08T16:38:25+00:00 |
|  | [Exhaust_cover_SFS](Fiction/Exhaust_cover_SFS) | Exhaust cover and BTT Smart Filament Sensor mount | V2.4, VT | 2024-01-08T16:38:25+00:00 |
|  | [LGX Lite toolhead PCB mount](Fiction/LGX_Lite_toolhead_PCB_mount) | Mount for Hartk's toolhead PCB(s) for LGX Lite | V1.8, V2.4, VSW, VT | 2024-01-08T16:38:25+00:00 |
| filotto78 | [6mm slot cover](filotto78/6mm_slot_cover) | Simple cover for extrusion with 6mm slot width | V2.4 | 2024-01-08T16:38:25+00:00 |
| frankaf | [Euclid Probe Carriage](frankaf/mgn12-euclid) | A MGN-12 carriage with an inset mount for a Euclid Probe | V1.8, V2.4, VT | 2024-01-08T16:38:25+00:00 |
| FreeformFez | [V1.8 Filtered Power Inlet](FreeformFez/FilteredPower) | V1.6 Filtered Inlet and Rocker Switch for V1.8 | V1.8 | 2024-01-08T16:38:25+00:00 |
| GadgetAngel | [Bed Support Extrusions Alignment...](GadgetAngel/Bed_Support_Alignment_Tools) | The bed support alignment tools will assist in helping align the... | V2.4 | 2024-01-08T16:38:25+00:00 |
|  | [Cricut Voron Logos](GadgetAngel/Cricut_Voron_Logos) | For any cutting machines or machines that rely on vector graphics... | V0.2, V2.4, VSW, VT | 2024-01-08T16:38:25+00:00 |
| Galvanic | [Bowden Tube Guide](Galvanic/Bowden_Tube_Guide) | Bowden tube guide and CANBUS wire support | V1.8, V2.4, VT | 2024-01-08T16:38:25+00:00 |
| gamebofh | [Laser cut door panels](gamebofh/door-panels) | Files to allow you to create laser cut door panels with some... | VSW | 2024-01-08T16:38:25+00:00 |
| gauravmm | [Crazy Mozzie HF toolhead SB+CW2](gauravmm/crazy_mozzie_cw2) | Toolhead for Crazy Mozzie HF, compatible with Stealthburner and... | V1.8, V2.4, VSW, VT | 2024-01-08T16:38:25+00:00 |
| gen2eng | [Switchwire LED wire pass through](gen2eng/z_carriage_stop_pass_through) | Z Carriage Stop modification that makes pass through of wires for... | VSW | 2024-01-08T16:38:25+00:00 |
| geoffreyyoung | [Dual Rail Installation Guide](geoffreyyoung/dual_rail_guide) | Rail installation guide that also works for the 2.4 dual rail... | V2.4 | 2024-01-08T16:38:25+00:00 |
|  | [LGX Info, Links, and Models](geoffreyyoung/lgx) | Useful information and models for using the Bondtech LGX extruder... | V1.8, V2.4, VSW, VT | 2024-01-08T16:38:25+00:00 |
| gerritwellen | [Manta M8P Mount](gerritwellen/manta-m8p-bracket) | Mounting Bracket for BTT Manta M8P | V2.4, VT | 2024-01-08T16:38:25+00:00 |
| GiulianoM | [Fly F407ZG Mount](GiulianoM/FlyF407ZG) | Mount for the Fly F407ZG: https://github.com/FLYmaker/FLYF407ZG | V2.4 | 2024-01-08T16:38:25+00:00 |
| Gizzle | [Ender 3 and Ender 3 Pro...](Gizzle/ender-3_pro_switchwire) | Mod for the Ender 3 and Ender 3 Pro, which adapts the kinematics... | VSW | 2024-01-08T16:38:25+00:00 |
| golas | [V0.1 Extended tophat hinge](golas/v0-extended-tophat-hinge) | Extended tophat for v0.1 with hinges (integrated or screwed ones). | V0.2 | 2024-01-08T16:38:25+00:00 |
|  | [V0.1 Trident skirt remix with...](golas/v0-trident-skirt-mix) | Trident style v0.1 skirt mix with 12864 Mini Lcd on front or plain... | V0.2 | 2024-01-08T16:38:25+00:00 |
| GSL12 | [Pocketwatch Nema 17](GSL12/pocketwatch_nema17) | Extruder like Pocketwatch, but with Nema17 instead of Nema14. Maybe... | V0 | 2024-01-21T20:17:15+00:00 |
| hartk1213 | [Voron0.2 2.8 Waveshare Display](hartk1213/Voron0.2_2.8_WaveshareDisplay) | 2.8 Waveshare display for V0.2 | V0.2 | 2025-05-29T01:45:55+00:00 |
|  | [Voron0.2 Rear Keystone Skirt](hartk1213/Voron0.2_Rear_Keystone_Skirt) | Added keystone slot on rear skirt for V0.2 | V0.2 | 2024-01-08T16:38:25+00:00 |
|  | [Voron0 C14Inlet](hartk1213/Voron0_C14Inlet) | Added a new Power inlet that uses a Fused C14 plug and switch that... | V0.1 | 2024-01-08T16:38:25+00:00 |
|  | [Voron0 deck panel](hartk1213/Voron0_deck_panel_with_logo_and_VORON0) | Used @Kruppes blank deck panel to add the logo as well as the name... | V0.1 | 2024-01-08T16:38:25+00:00 |
|  | [Voron0 display dualcolor](hartk1213/Voron0_display_dualcolor) | Added a dual color file for the Voron Display Front housing | V0.1 | 2024-01-08T16:38:25+00:00 |
|  | [Voron0 ExtendedLegs](hartk1213/Voron0_ExtendedLegs) | New extended legs to raise the printer up a tiny bit more | V0.1 | 2024-01-08T16:38:25+00:00 |
|  | [Voron0 ExtrusionSkirt](hartk1213/Voron0_ExtrusionSkirt) | Created a new skirt design that uses 50mm extrusions as legs and it... | V0.1 | 2024-01-08T16:38:25+00:00 |
|  | [Voron0 Hinged Top Hat](hartk1213/Voron0_Hinged_Top_Hat) | Created a new hinged top hat design for the V0 so it can fold away... | V0.1 | 2024-01-08T16:38:25+00:00 |
|  | [Voron0 MGN9C X Axis](hartk1213/Voron0_MGN9C_X_Axis) | This mod, replaces the stock MGN7H for MGN9C on the V0 | V0.1 | 2024-01-08T16:38:25+00:00 |
|  | [Voron2.4 GE5C](hartk1213/Voron2.4_GE5C) | This mod replaces the stack of printed z joints with a metal... | V2.4 | 2024-01-08T16:38:25+00:00 |
|  | [Voron2.4 SexBolt ZEndstop](hartk1213/Voron2.4_SexBolt_ZEndstop) | This mod replaces stock V2 Z endstop with a different style | V2.4, VT | 2024-01-08T16:38:25+00:00 |
|  | [Voron2.4 and Trident Pins Mod](hartk1213/Voron2.4_Trident_Pins_Mod) | This mod replaces all the M5 screws for all idlers/pulleys/bearings... | V2.4, VT | 2024-01-08T16:38:25+00:00 |
|  | [Voron2.4 Y Endstop Relocation](hartk1213/Voron2.4_Y_Endstop_Relocation) | This mod relocates the Y endstop to the top A drive piece | V2.4 | 2024-01-08T16:38:25+00:00 |
| henrikssn | [Parametric Spool Holder](henrikssn/parametric_spool_holder) | Spool holder where the length is a parameter. | V1.8, V2.4, VT | 2024-01-08T16:38:25+00:00 |
|  | [Plug Panel Mod for Generic...](henrikssn/plug_panel_generic) | v2.4 plug panel for generic unfiltered modules with 66mm x 27mm... | V2.4 | 2024-01-08T16:38:25+00:00 |
| hergtoler | [Exhaust Housing for 120mm Fan...](hergtoler/exhaust_120mm_duct) | v2.4 Exhaust Housing for 120mm Fan and 4in Duct | V2.4 | 2024-01-08T16:38:25+00:00 |
| hernsl | [Bottom Panel Mag Clip](hernsl/bottom_panel_mag_clip) | v2.4 magnetic clips to retain bottom panel | V2.4 | 2024-01-08T16:38:25+00:00 |
| hhammarstrand | [Afterburner connector cover for...](hhammarstrand/afterburner_connector_cover_42STH20-1004AS) | Connector cover for 42STH20-1004AS | VSW | 2024-01-08T16:38:25+00:00 |
| hijax_pl | [Corner panel clip](hijax_pl/corner_panel_clip) | V2 panel corner frames using 3-way L brackets in the corners | V2.4 | 2024-01-08T16:38:25+00:00 |
|  | [Din Rail mount](hijax_pl/din_rail_mount) | Adapter to attach DIN Rail to 2020 extrusion. | V2.4 | 2024-01-08T16:38:25+00:00 |
|  | [Controler Board adapters](hijax_pl/ender_compatible_controller_mount) | DIN (rotated) and legacy adapters for boards like SKR mini E3. | V2.4 | 2024-01-08T16:38:25+00:00 |
| Hobson318 | [Belt Tension Wrench](Hobson318/Belt_Tension_Wrench) | Wrench for easier turning of the belt tension knobs on V0.1 | V0.2 | 2024-01-08T16:38:25+00:00 |
|  | [Klipper Expander Mount](Hobson318/Klipper_Expander_Mount) | Mounting brackets for the klipper expander using vhb tape or... | V0.2, V1.8, V2.4, VSW, VT | 2024-01-08T16:38:25+00:00 |
| hoschi | [FYSETC Spider DIN Rail Mount](hoschi/FYSETC_Spider_DIN_Mount) | DIN rail mount for FYSETC Spider | V2.4 | 2024-01-08T16:38:25+00:00 |
| hymness1 | [10x11mm chain VSW](hymness1/10x11mm_chain_VSW) | Printable and openable 10x11mm chain | V0.2, VSW | 2024-01-08T16:38:25+00:00 |
|  | [Quickdraw probe Voron Switchwire](hymness1/Quickdraw_probe_Voron_Switchwire) | Detachable magnetic probe with docking system for VSW | VSW | 2024-01-08T16:38:25+00:00 |
| Iakabos | [c920 Mount](Iakabos/C920_mount) | Slim mount for logitech c920 webcam | V1.8, V2.4 | 2024-01-08T16:38:25+00:00 |
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
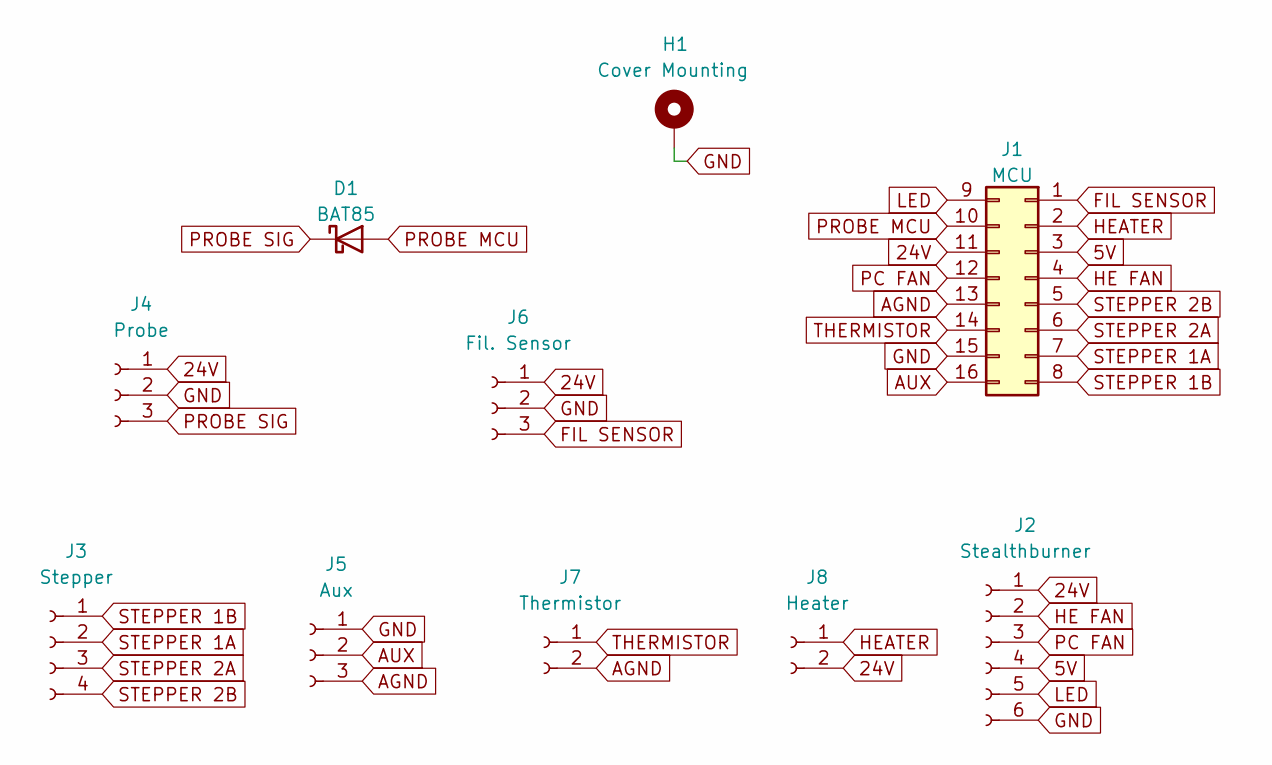
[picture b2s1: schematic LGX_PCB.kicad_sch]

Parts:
D1: BAT85; D_DO-35_SOD27_P7.62mm_Horizontal
H1: Cover Mounting; MountingHole_3.2mm_M3_Pad
J1: MCU; Molex_Micro-Fit_3.0_43045-1600
J2: Stealthburner; PinSocket_1x06_P2.54mm_Horizontal
J3: Stepper; JST_PH_B4B-PH-K_1x04_P2.00mm_Vertical
J4: Probe; JST_PH_B3B-PH-K_1x03_P2.00mm_Vertical
J5: Aux; JST_PH_B3B-PH-K_1x03_P2.00mm_Vertical
J6: Fil. Sensor; JST_PH_B3B-PH-K_1x03_P2.00mm_Vertical
J7: Thermistor; Molex_Micro-Fit_3.0_43650-0200
J8: Heater; Molex_Micro-Fit_3.0_43650-0200

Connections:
5V: J1.3, J2.4
24V: J1.11, J2.1, J4.1, J6.1, J8.2
AGND: J1.13, J5.3, J7.2
AUX: J1.16, J5.2
FIL SENSOR: J1.1, J6.3
GND: H1.1, J1.15, J2.6, J4.2, J5.1, J6.2
HE FAN: J1.4, J2.2
HEATER: J1.2, J8.1
LED: J1.9, J2.5
PC FAN: J1.12, J2.3
PROBE MCU: D1.2 (A), J1.10
PROBE SIG: D1.1 (K), J4.3
STEPPER 1A: J1.7, J3.2
STEPPER 1B: J1.8, J3.1
STEPPER 2A: J1.6, J3.3
STEPPER 2B: J1.5, J3.4
THERMISTOR: J1.14, J7.1

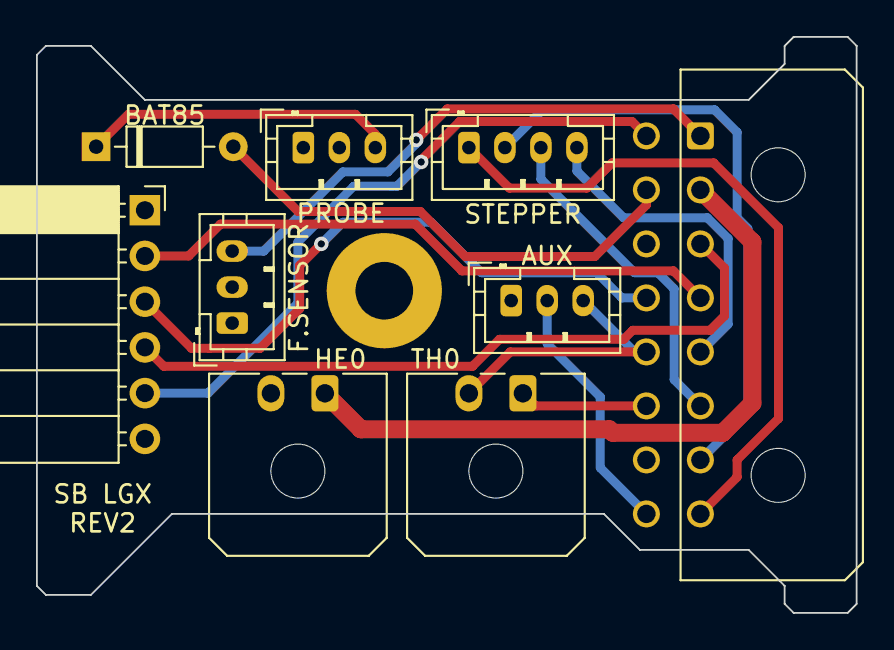
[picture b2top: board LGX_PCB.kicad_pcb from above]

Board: 4 copper layers, 45.5 x 32.0 mm, 10 parts (0 on the bottom side), 17 nets.

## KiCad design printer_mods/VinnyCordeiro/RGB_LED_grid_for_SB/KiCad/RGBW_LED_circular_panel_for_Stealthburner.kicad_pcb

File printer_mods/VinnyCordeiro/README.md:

VinnyCordeiro's mods for Voron printers.

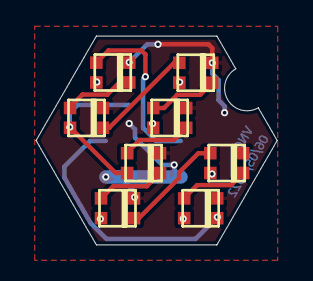
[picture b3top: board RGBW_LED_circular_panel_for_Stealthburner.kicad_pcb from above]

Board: 2 copper layers, 13.4 x 11.6 mm, 9 parts (1 on the bottom side), 11 nets.

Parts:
D1, D2, D3, D4, D5, D6, D7, D8: WS2812B; WS2812B-2020
J1: Conn_02x03_Odd_Even; Pin_Header_Straight_2x03_Pitch2.00mm_SMD

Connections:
+5V: D1.1 (VDD), D2.1 (VDD), D3.1 (VDD), D4.1 (VDD), D5.1 (VDD), D6.1 (VDD), D7.1 (VDD), D8.1 (VDD), J1.1, J1.2
GND: D1.3 (VSS), D2.3 (VSS), D3.3 (VSS), D4.3 (VSS), D5.3 (VSS), D6.3 (VSS), D7.3 (VSS), D8.3 (VSS), J1.5, J1.6
LED_IN: D1.4 (DIN), J1.3
LED_OUT: D8.2 (DOUT), J1.4
unnamed: D1.2 (DOUT), D2.4 (DIN)
unnamed: D3.2 (DOUT), D4.4 (DIN)
unnamed: D4.2 (DOUT), D5.4 (DIN)
unnamed: D5.2 (DOUT), D6.4 (DIN)
unnamed: D7.2 (DOUT), D8.4 (DIN)
R1_R2: D2.2 (DOUT), D3.4 (DIN)
R2_R3: D6.2 (DOUT), D7.4 (DIN)

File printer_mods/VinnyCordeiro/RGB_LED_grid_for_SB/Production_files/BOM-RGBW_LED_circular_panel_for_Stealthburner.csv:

Comment,Designator,Footprint,LCSC
WS2812B,"D1,D2,D3,D4,D5,D6,D7,D8",WS2812B-2020,C965555
Conn_02x03_Odd_Even,J1,Pin_Header_Straight_2x03_Pitch2.00mm_SMD,

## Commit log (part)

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2023-12-25 Remove label check from pull_request_ci.yml
2023-12-25 initial add
2023-12-25 Minor updates to follow submissions rules
2023-12-25 Update README.md
    updated to relative images
2023-12-25 replacing STEP file with chamfers
2023-12-25 Delete printer_mods/dankeeling/CreativeLiveCameraMount/Images/20231224_211032~2.jpg
    Replacing with underscore
2023-12-25 Update .metadata.yml
    Cleaning up filenames
2023-12-25 Update README.md
    cleanup of URL
2023-12-25 Create Folder
2023-12-26 Update README.md
    changed video link to link to youtube
2023-12-26 Update README.md
    Updated YouTube link description
2023-12-26 Toolhead for Phaetus Dragon UHF/UHF mini (#1013)
2023-12-26 Generate VoronUsers README
    [skip ci]
2023-12-27 V0 Electronics Bay Modesty Mesh (#1014)
2023-12-27 Add Umbilical Collar
2023-12-27 Universal Phone mount by AVieira-1 (#1017)
    * Create metadata.yml
    * Create metadata.yml
    * Add files via upload
    * Delete printer_mods/AVieira/metadata.yml
    * Update README.md
    * Update README.md
2023-12-27 V0 Umbilical Collar by MapleLeafMakers (#1020)
2023-12-27 V0 Stealth Handles by MapleLeafMakers (#1019)
2023-12-27 Add V0 Upper Rear Bowden Inlet (URBI)
2023-12-28 Add 0.4mm bottom chamfer to all parts
2023-12-28 update compatibility in readme
2023-12-28 Add V0 Upper Rear Bowden Inlet (URBI) (#1021)
2023-12-28 Update modesty-mesh readme (#1022)
2023-12-29 Add Rainbow Serial Bumper for Trident
2023-12-29 add .metadata.yml
2023-12-29 remove unused thumbnail.png
2023-12-29 remove thumbnail.png from .metadata.yml
2023-12-29 Add Rainbow Serial Bumper for Trident (#1023)
2023-12-30 Backplates for Voron 2.4
2023-12-30 Structured
2023-12-30 Renamed structure
2023-12-30 Renamed the files and added STEP
2023-12-30 Placed the yml in the correct folder
2023-12-30 First upload
2023-12-30 Creative Live! Camera Mount by DanKeeling (#1018)
    * initial add
    * Update README.md
    * Minor updates to follow submissions rules
    * Add files via upload
    * Update README.md
    * Add files via upload
2023-12-30 fix typo in .metadata.yml
2023-12-30 add 0.4mm bottom chamfer to some carriers
2023-12-30 Matchstick Diffusers by MapleLeafMakers (#1025)
2023-12-31 Kirigami Stealth Bumper by MapleLeafMakers (#1028)
    * Add Kirigami Stealth Bumper
    * fix typo in .metadata.yml
    * add 0.4mm bottom chamfer to some carriers
2024-01-01 2.4 Bedfan Backplates by Ferdi360 (#1027)
    * First upload
    * Resolved requested changes
    * Update printer_mods/Ferdi360/2.4_Bedfan_Backplates/.metadata.yml
    * Update printer_mods/Ferdi360/2.4_Bedfan_Backplates/README.md
    ---------
2024-01-03 add sample mod
2024-01-04 remove render
2024-01-09 Re-generate VoronUsers README with latest changes
    [skip ci]
2024-01-09 add stls to metadata
2024-01-15 add VSW and VL to compatibility
2024-01-18 Update README.md and add new banner by @hartk1213
2024-01-18 Add issue template for mod adoption
    [skip ci]
2024-01-21 Fix mods without printer compatibility
2024-01-21 Flush mount for hdmi and usb c (#1)
    * Adds CAD and STL files for flush mount mod.
    * Renames mod folder name.
    * Updates dimensions of flush mount opening.
    * Adds photos and updates `README.md`.
2024-01-22 Adds image for BATIGE Mount.
2024-01-23 Removes possibly copyright image and updates `metadata.yml`.
2024-01-23 Updates `README.md` to no longer use `html`.
2024-01-23 Adds `All_Sizes_2` in `README.md`.
2024-01-25 Flush mount for hdmi and usb c by ppak10 (#1031)
    * Flush mount for hdmi and usb c (#1)
    * Adds CAD and STL files for flush mount mod.
    * Renames mod folder name.
    * Updates dimensions of flush mount opening.
    * Adds photos and updates `README.md`.
    * Reduces `.stl` size, adds `0.4 mm` chamfer, and notes installation.
2024-02-01 5160T Plus Mounts, LRS DIN Mount Offset and Lever Connector Mount Side Fan Support by Dr-Info (#1033)
    * Create README.md
    * Create mounts_btt_5160t_plus.step
    * Add files via upload
    * Create 30mm_fan_shroud_5160T_plus_x2.stl
    * Add files via upload
    * Create 1515_bracket_5160T_plus.stl
2024-02-18 Mod Adoption: Dr-Info adopts V2.4 Z drive tensioner from edwardyeeks
2024-02-22 Mod for the skirts to resolve collision
    Skirts are interfering with the screen mount. Let's cut the skirt
2024-02-22 Added 300 and 350mm skirts mod
    Cut the bit from skirts to resolve the interference with screen frame
2024-02-22 Added the full assembly reference and an update to readme
    Added the note about non-standard skirts requirement
2024-02-23 Mod Adoption: Dr-Info adopts V2.4 Z drive tensioner from edwardyeeks (#1034)
2024-02-29 Add CAD Files for most xbst mods
2024-02-29 whitespace cleanup
2024-02-29 fix cad listing in .metadata.yml
2024-03-09 2020 aplic cam mount
2024-03-09 moved to subfolder
2024-03-09 deleted duplicates
2024-03-09 fixed typos
2024-03-10 renamed metadata.yml, added shortened version, removed stl import
2024-03-10 fixed PR issues
2024-03-10 corrected typos/quantities in BOM
2024-03-14 Add CAD Files for most xbst mods (#1036)
    * Add CAD Files for most xbst mods
    * whitespace cleanup
    * fix cad listing in .metadata.yml
2024-03-14 2020 aplic cam mount by techprolet (#1039)
    * 2020 aplic cam mount
    * renamed metadata.yml, added shortened version, removed stl import
    * fixed PR issues
    * corrected typos/quantities in BOM
    * fixed typose, added M3 spacer length
    ---------
2024-03-14 add CAD for khay mods (#1037)
2024-03-25 feat: add switchwire cyd screen case files
2024-03-26 fix: change orientation for best print
2024-03-27 fix: add bridging to counterbored holes
2024-03-31 add switchwire cyd screen case files by Reemuson (#1041)
    * feat: add switchwire cyd screen case files
    * docs: added gif to README
    * fix: change orientation for best print
    * fix: add bridging to counterbored holes
2024-04-28 Create README.md
    Initial page for mod variation
2024-04-28 Create README.md
    Create page for mod variation
2024-04-28 Create README.md
    added page for mod
2024-05-02 moving readme.md file in the correct folder
2024-05-07 Adds CAD, STL, and Images.
2024-05-07 Adds images and description to files.
2024-05-07 Updates `.metadata.yml` with correct `.STL` file links and fixes stls.
2024-05-09 Update README.MD
    Removed Paypal link
2024-05-12 corrected the errors
    - shrieked the file size
    - corrected corrupted files
    - updated yml file
    - added Rapido UHF
2024-05-12 Shorter description
2024-05-13 assembley pictures
2024-05-13 assembly.md
2024-05-13 updated assembly.md
2024-05-13 assembley.md
    adding guide how to assemble the toolhead
2024-05-13 updated style
2024-05-13 updated image style
2024-05-13 Update v6_heatsink_mod.md
    Grammar
2024-05-13 Update toolhead_assembly.md
    explained the steps
2024-05-15 Update metadata.yml & added readme
2024-05-16 Upload STL and CAD. Update metadata.yml
2024-05-16 Update STLs orientation
2024-05-16 Added images and completed the README.md
2024-05-16 Add alt text to images
2024-05-16 Fixed image path typo in metadata.yml. Removed f3z file, lighten the step file removing unecessary components.
2024-05-18 Add gallery images to metadata.yml file
2024-05-19 Change name Extruder to Extrusion
2024-05-20 left STL to Binary
2024-05-22 yml updated
2024-05-22 removed the 7z archive
2024-05-23 Create a new directory
2024-05-23 Removed old directory
2024-06-04 initial
2024-06-06 fixed linting errors
2024-06-17 fixed image links in metadata
2024-06-19 Ballpoint pen spring DIN clips assortment by aeresov (#1048)
    * initial
    * fixed linting errors
    * fixed image links in metadata
2024-07-02 WAGO_221-415_mount_3x5_M3_fasteners
    And here's the second one I'd like to submit.
2024-07-02 removed separate mod
    removed another mod I want to submit.
2024-07-02 WAGO_221-415_mount_3x5_M3_fasteners
    This is a reworked WAGO mount using M3 fasteners instead of M5, it is also a bit thinner so it fits between DIN rails easier.
2024-07-02 Changes
    Changed discord_username
2024-07-02 Corrected?
    I removed an empty line in the description that was used to space the sentences, maybe that fixed it?
2024-07-02 Punctuation correction
    Forgot to add a space after a period in description, corrected.
2024-07-02 pre-emptive correction
    removed an empty line for spacing sentences in description.
2024-07-02 Shortened Description
    Shortened description per advice on other mod submission.
2024-07-04 Rs 50 5 bracket by Rikers-Beard (#1050)
    * RS-50-5 Bracket
    This is my first attempt at submitting a mod, sorry if I messed anything up!
    * WAGO_221-415_mount_3x5_M3_fasteners
    And here's the second one I'd like to submit.
    * removed separate mod
    removed another mod I want to submit.
2024-07-12 Publish ‘Double_GEAR_ratio_Z’
2024-07-13 Add Assemble Instructions，Resize photo
2024-07-14 edit read me and YAML file
2024-07-14 fix Voron LOGO for stl， change description in readme
2024-07-14 Double_GEAR_ratio_Z by zzp8202 (#1052)
    * Publish ‘Double_GEAR_ratio_Z’
    * add photo
    * Add Assemble Instructions，Resize photo
    * Update Z_Belt_Clamp_Upper_x8.STL
    * edit read me and YAML file
    * fix Voron LOGO for stl， change description in readme
2024-09-22 Orientation for printing
2024-09-22 New mod : PEI Stop
2024-09-24 PEI Stop by Itzo1978 (#1055)
2024-10-03 use native Jinja variable _bucket_pos
    The previous implementation of dynamically changing bucket_pos on each
    run had an extremely confusing semantic of changing the variable early
    in the execution of the macro but see the effect only on the next run of
    the macro. This led to the situation that the first bucket position
    after the machine started was never selected randomly, only all later
    ones. While this for sure is not a major problem of the implementation
2024-10-03 variable_bucket_park: select bucket to park nozzle after cleaning
    The previous implementation always parked the nozzle over the left
    bucket after cleaning. While this makes sense in most cases it is
    problematic when you happen to have something installed over the left
    bucket, like the Klicky Probe. If parking the nozzle over the Klicky
    Probe there is a certain risk to pull it out of the docking station by
    accident with the move command following the cleaning procedure. When
2024-10-03 variable_bucket_purge: select bucket for purging
    In the original implementation, the bucket for purging was selected
    randomly. Since I wanted to park the nozzle always over the right
    bucket to avoid conflicts with the Klicky Probe and as such always
    oozing into that (on my 350 build) smaller right bucket I thought that
    it might be useful to compensate for this by always purging to the
    larger left bucket.
2024-10-06 Update orphaned_mods/edwardyeeks/Decontaminator_Purge_Bucket_&_Nozzle_Scrubber/Macros/ by schiele (#1057)
    * use native Jinja variable _bucket_pos
    The previous implementation of dynamically changing bucket_pos on each
    run had an extremely confusing semantic of changing the variable early
    in the execution of the macro but see the effect only on the next run of
    the macro. This led to the situation that the first bucket position
    after the machine started was never selected randomly, only all later
2024-10-14 Actually corrected the issues this time.
    I had STLs instead of STL and images instead of Images. Hopefully that's all it was!
2024-11-28 Update nozzlewiper.cfg - Wait for servo move before turning off
    The servo was turned off before it reached target angle.
2024-12-01 Updated as requested
    updated file names and formatting.
2024-12-02 Fix metadata.yml, add updated CAD files, update readme
2024-12-02 Remove M4P from step file, reorient parts for printing
2024-12-02 Add bom and instructions to README, update metadata
2024-12-09 New modded printhead v1
    pictures, stl, etc.
2025-03-29 v0 Foldable Display Mount
2025-03-29 Remove two unnecessary lines from the template that were mistakenly left in.
    Thanks to mjonuschat for spotting this.
2025-03-29 Update the README.
2025-04-05 Gantry And Wire Friendly Flush Extrusion Cover
    Gantry And Wire Friendly Flush Extrusion Cover UserMod submitted
2025-05-09 Added an ethernet adapter.
2025-05-28 Update README.md
    use new auto install script
2025-05-29 Update README.md (#1068)
    use new auto install script
2025-06-21 Rename 20250621_143212494[1].JPG to pic.JPG
2025-06-21 Rename pic.JPG to pic.jpg
